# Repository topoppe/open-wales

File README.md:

# open-wales
Open-WaLeS: Ein Open-Source-IoT-System zur kurz- und langfristigen Überwachung von Binnenpegeln

Welcome to the official Github-Repo of the Open-WaLeS-System

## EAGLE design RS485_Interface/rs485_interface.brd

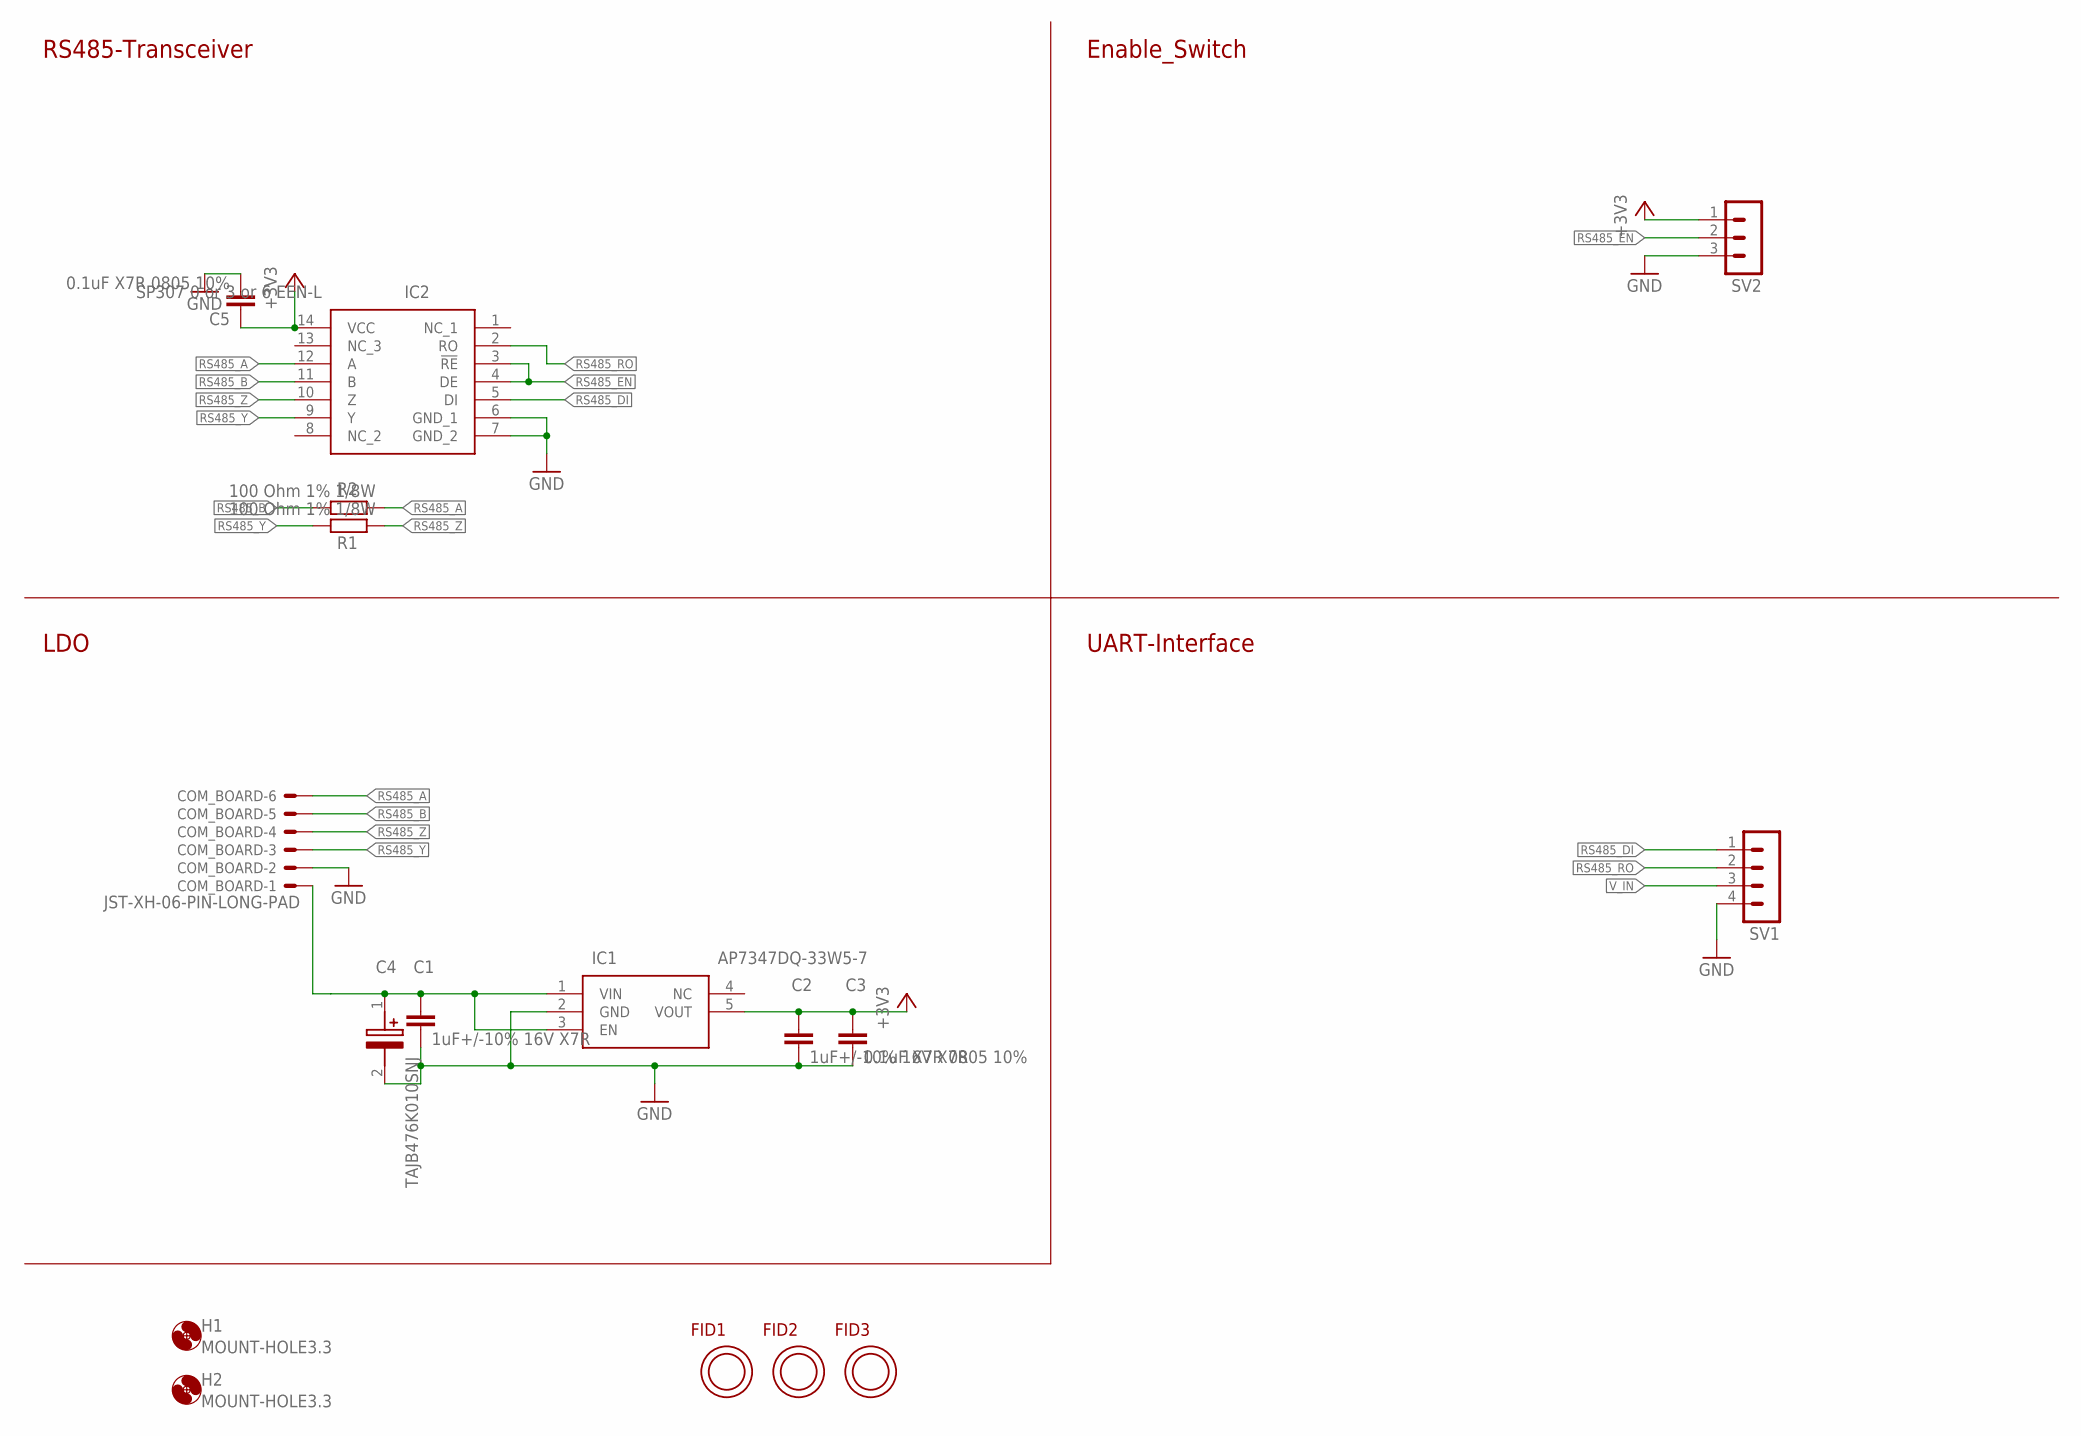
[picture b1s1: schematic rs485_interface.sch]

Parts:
C1, C2: 1uF+/-10% 16V X7R; C0805
C3, C5: 0.1uF X7R 0805 10%; C0805
C4: TAJB476K010SNJ; CAPPM3528X210N
COM_BOARD: JST-XH-06-PIN-LONG-PAD; JST-XH-06-PACKAGE-LONG-PAD
FID1, FID2, FID3: OPEN-PNP-FIDUCIAL
H1, H2: MOUNT-HOLE3.3; 3,3
IC1: AP7347DQ-33W5-7; SOT95P280X145-5N
IC2: SP307 0 or 3 or 6 EEN-L; SOIC127P600X175-14N
R1, R2: 100 Ohm 1% 1/8W; R0805
SV1: MA04-1
SV2: MA03-1

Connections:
+3V3: C2.1, C3.1, C5.1, IC1.5 (VOUT), IC2.14 (VCC), SV2.1
GND: C1.2, C2.2, C3.2, C4.2 (-), C5.2, COM_BOARD.2, IC1.2 (GND), IC2.6 (GND_1), IC2.7 (GND_2), SV1.4, SV2.3
RS485_A: COM_BOARD.6, IC2.12 (A), R2.1
RS485_B: COM_BOARD.5, IC2.11 (B), R2.2
RS485_DI: IC2.5 (DI), SV1.1
RS485_EN: IC2.3 (!RE), IC2.4 (DE), SV2.2
RS485_RO: IC2.2 (RO), SV1.2
RS485_Y: COM_BOARD.3, IC2.9 (Y), R1.2
RS485_Z: COM_BOARD.4, IC2.10 (Z), R1.1
V_IN: C1.1, C4.1 (+), COM_BOARD.1, IC1.1 (VIN), IC1.3 (EN), SV1.3

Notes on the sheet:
RS485-Transceiver
LDO
Enable_Switch
UART-Interface

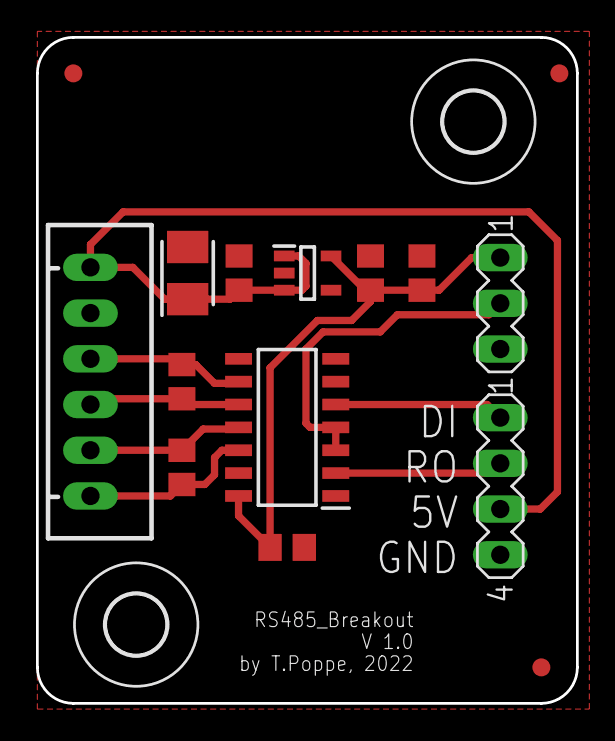
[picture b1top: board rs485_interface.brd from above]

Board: 2 copper layers, 30.0 x 37.0 mm, 17 parts (0 on the bottom side), 10 nets.

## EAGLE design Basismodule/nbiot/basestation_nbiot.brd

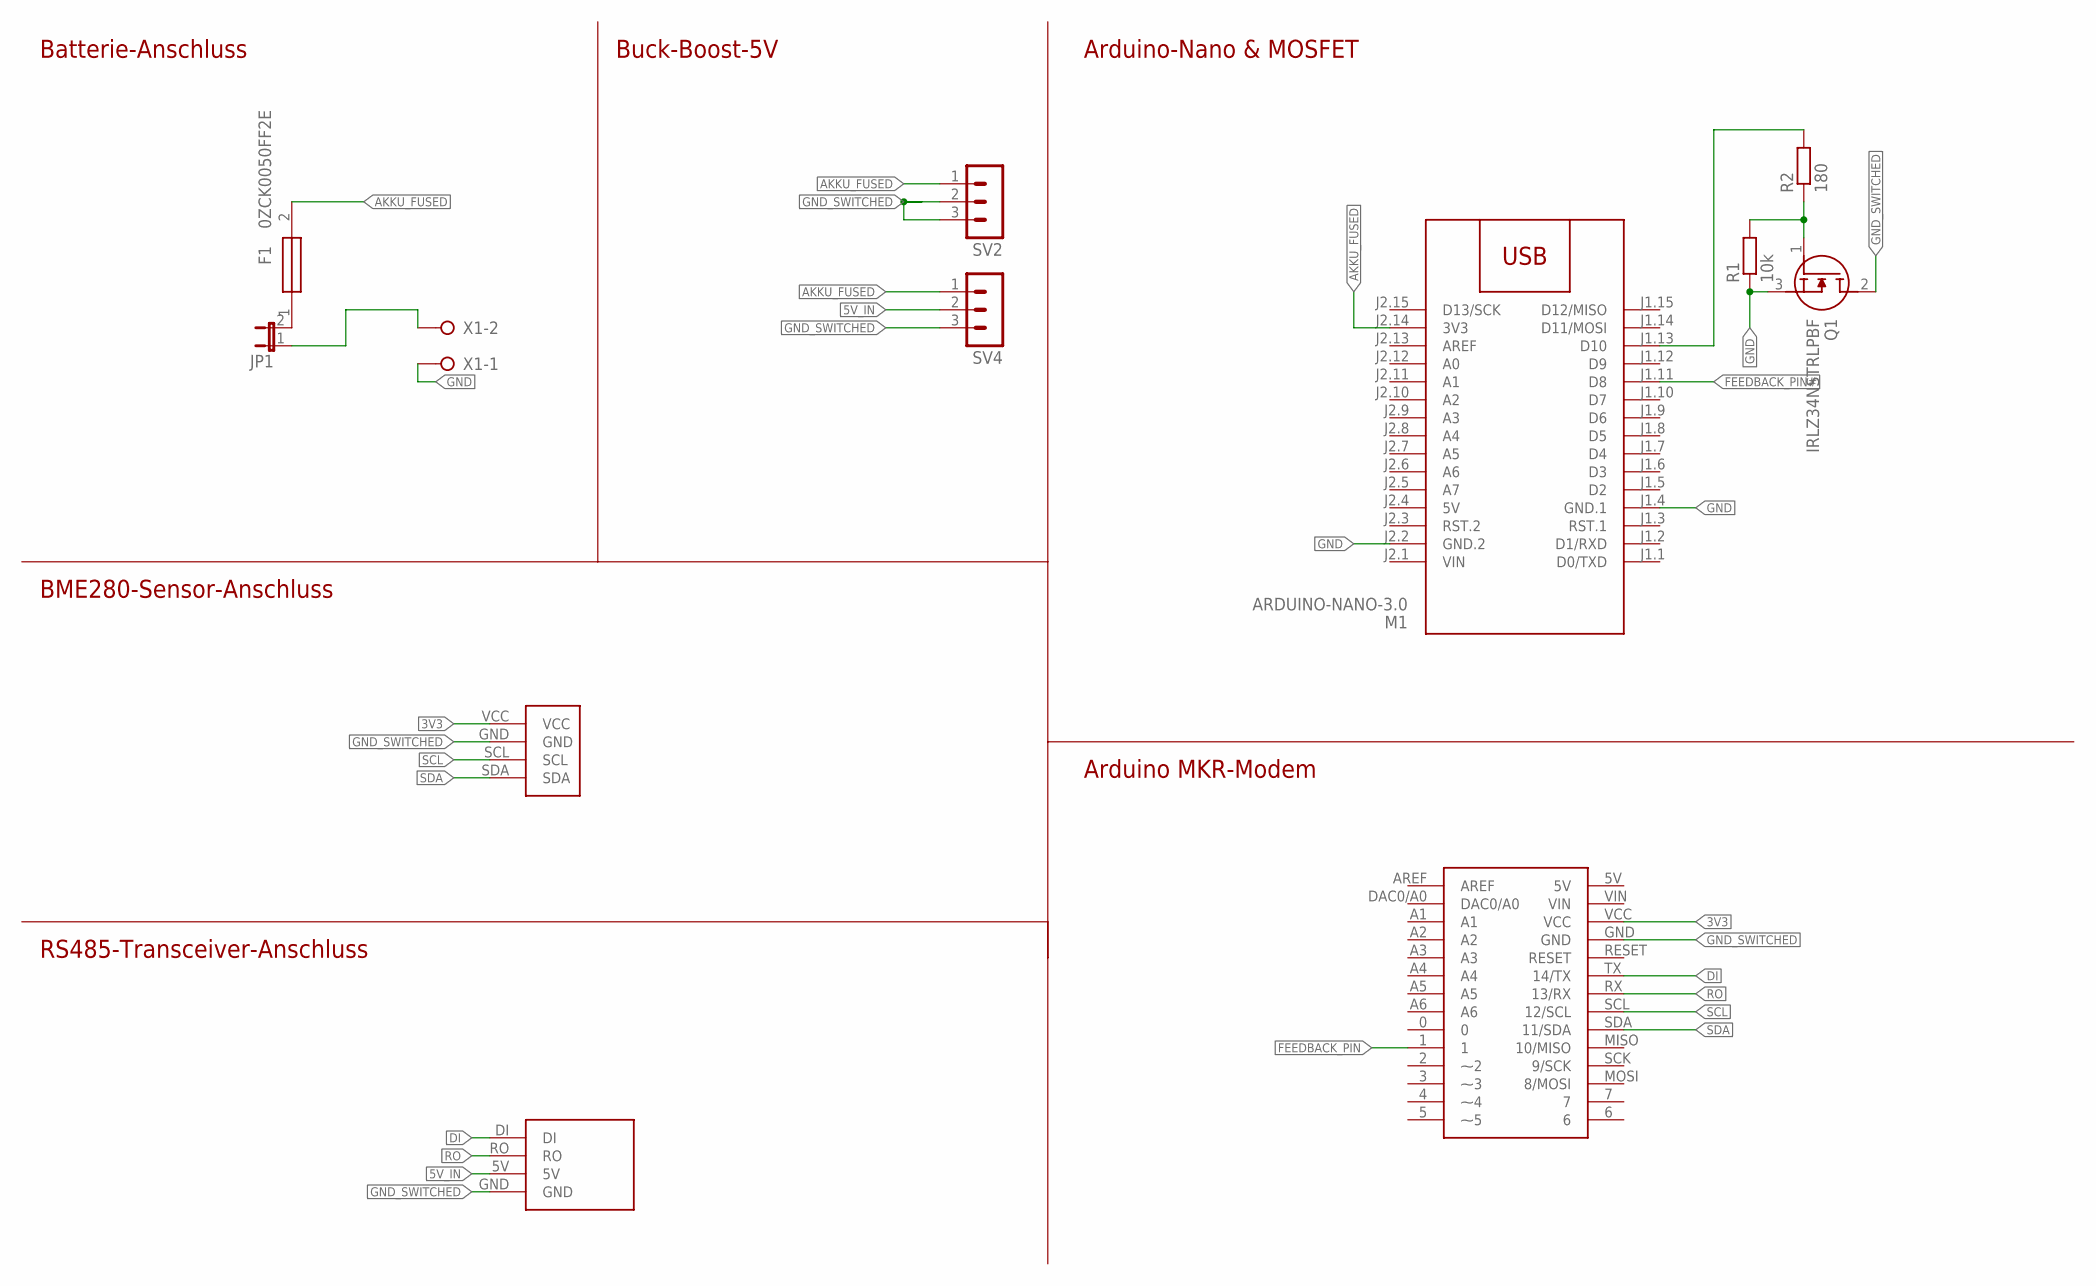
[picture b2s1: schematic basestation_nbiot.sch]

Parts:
F1: 0ZCK0050FF2E; FUSC2214X125N
JP1: JP1E; JP1
M1: ARDUINO-NANO-3.0
Q1: IRLZ34NSTRLPBF; D2PAK
R1: 10k; R1206
R2: 180; R1206
SV2, SV4: MA03-1
U$1: ARDUINO_GSM_MKR_1400; ARDUINO_GSM_MKR1400
U$2: BME280-BREAKOUT
U$3: RS485_PEGEL_BREAKOUT
X1: W237-02P; W237-132

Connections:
3V3: U$1.VCC, U$2.VCC
5V: M1.J2.4 (5V)
5V_IN: SV4.2, U$3.5V
AKKU_FUSED: F1.2, M1.J2.14 (3V3), SV2.1, SV4.1
AKKU_UNFUSED: JP1.1, X1.2
DI: U$1.TX (14/TX), U$3.DI
FEEDBACK_PIN: U$1.1
FEEDBACK_PIN#: M1.J1.11 (D8)
GND: M1.J1.4 (GND.1), M1.J2.2 (GND.2), Q1.3 (S), R1.1, X1.1
GND_SWITCHED: Q1.2 (D), SV2.2, SV2.3, SV4.3, U$1.GND, U$2.GND, U$3.GND
unnamed: M1.J1.13 (D10), R2.2
unnamed: Q1.1 (G), R1.2, R2.1
unnamed: F1.1, JP1.2
RO: U$1.RX (13/RX), U$3.RO
SCL: U$1.SCL (12/SCL), U$2.SCL
SDA: U$1.SDA (11/SDA), U$2.SDA
VIN: M1.J2.1 (VIN)

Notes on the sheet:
Batterie-Anschluss
Buck-Boost-5V
BME280-Sensor-Anschluss
RS485-Transceiver-Anschluss
Arduino-Nano & MOSFET
Arduino MKR-Modem

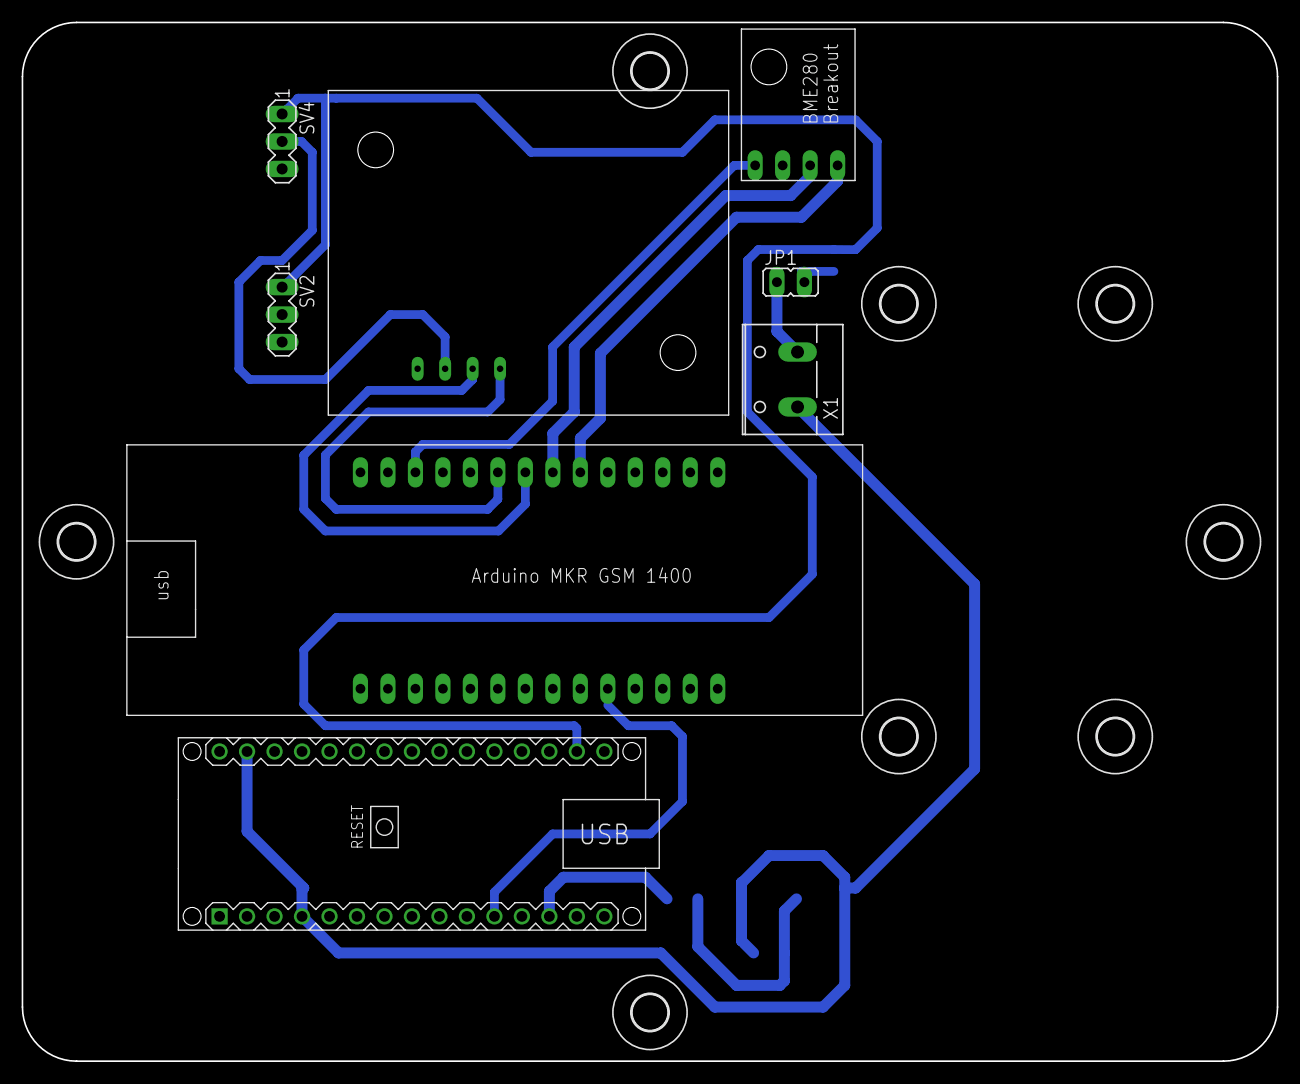
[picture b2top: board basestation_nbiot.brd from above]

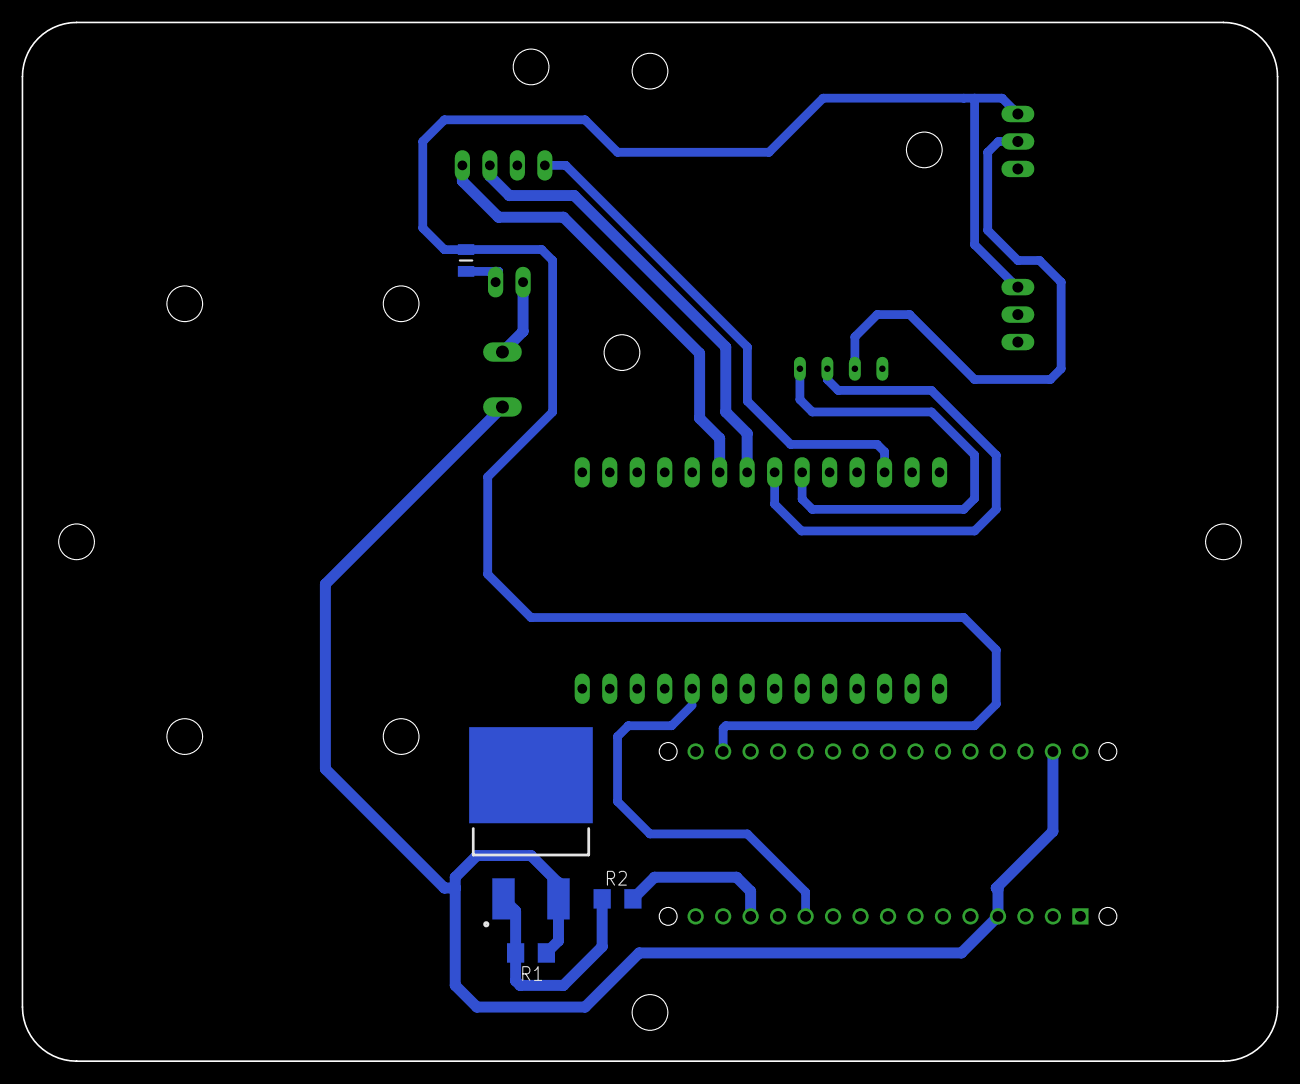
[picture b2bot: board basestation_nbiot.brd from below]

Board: 2 copper layers, 116.0 x 96.0 mm, 20 parts (4 on the bottom side), 13 nets.

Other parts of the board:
U$4, U$5, U$6, U$7, U$8, U$9, U$12, U$13: 3,3

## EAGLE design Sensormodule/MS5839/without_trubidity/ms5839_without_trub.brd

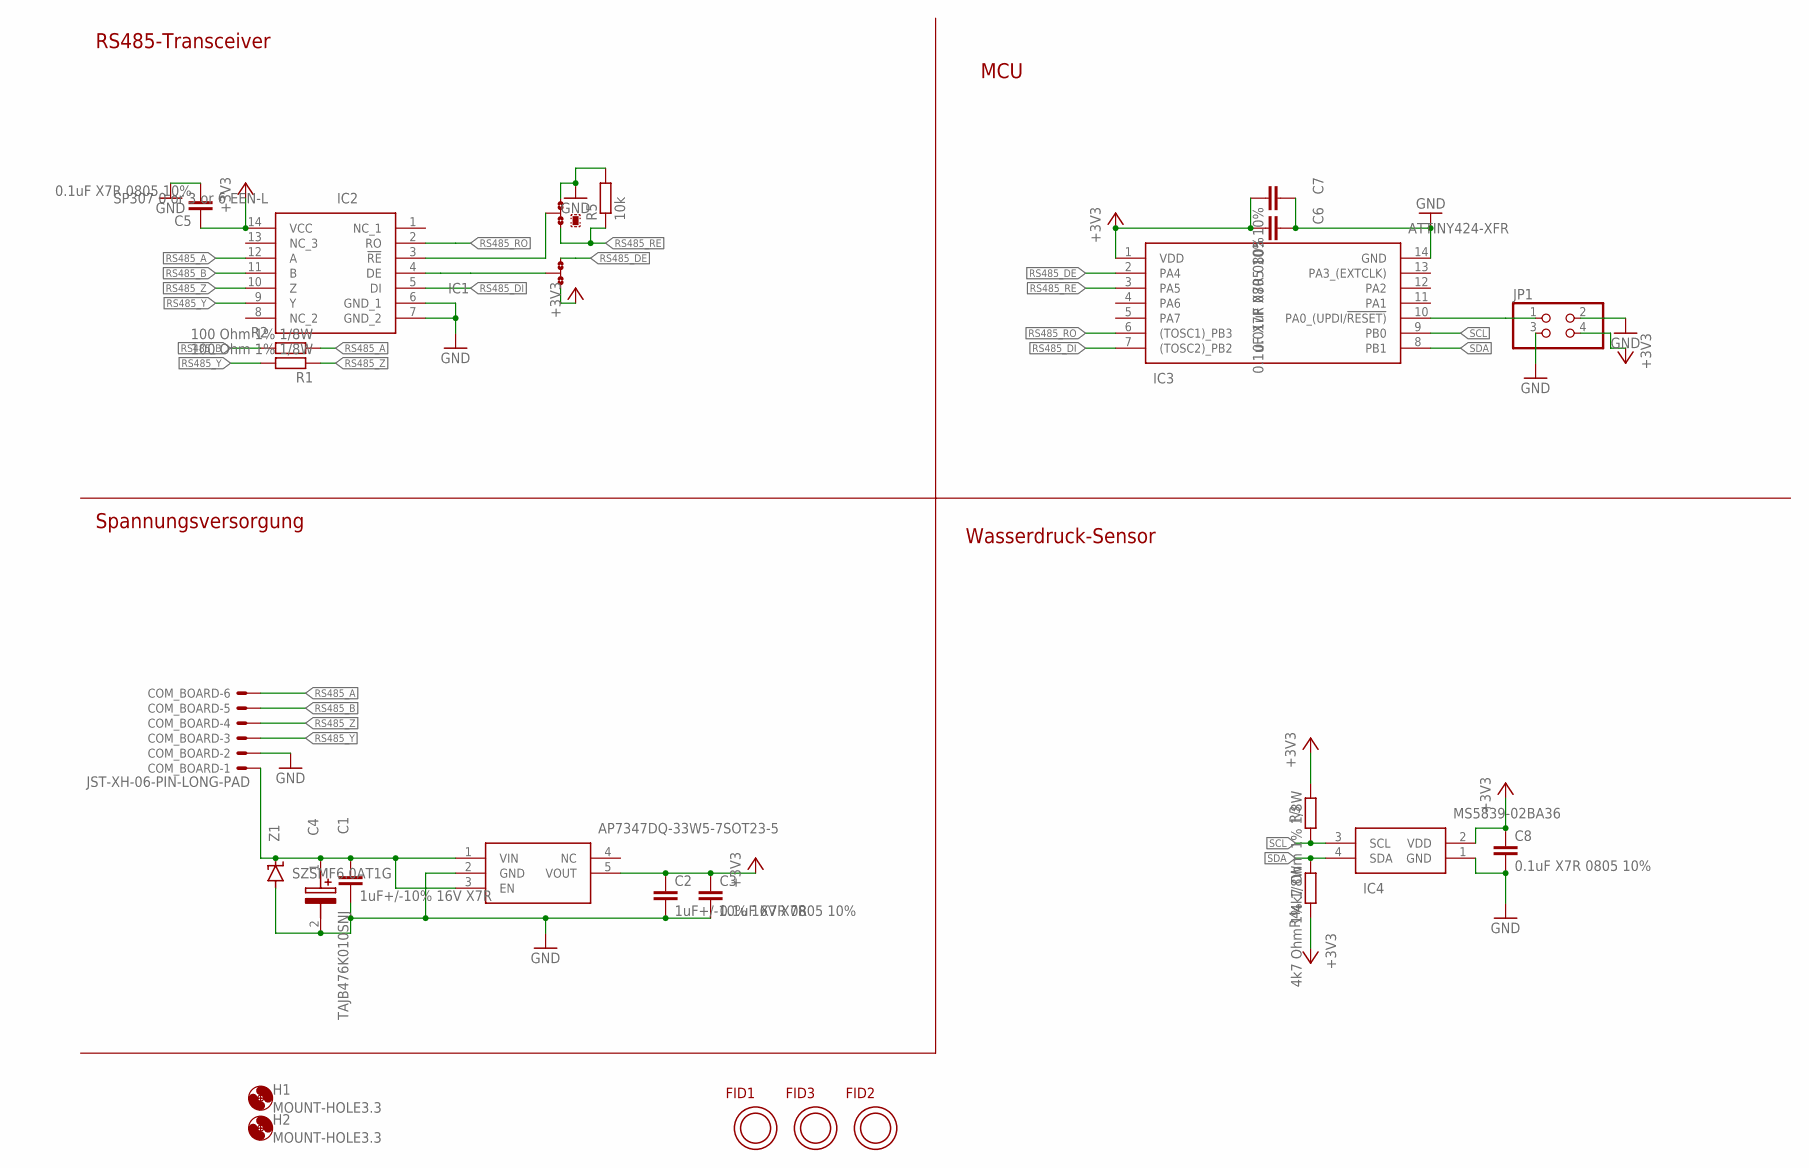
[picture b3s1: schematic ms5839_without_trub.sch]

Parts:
C1, C2: 1uF+/-10% 16V X7R; C0805
C3, C5, C6, C8: 0.1uF X7R 0805 10%; C0805
C4: TAJB476K010SNJ; CAPPM3528X210N
C7: 0.01uF X7R 0805 10%; C0805
COM_BOARD: JST-XH-06-PIN-LONG-PAD; JST-XH-06-PACKAGE-LONG-PAD
FID1, FID2, FID3: OPEN-PNP-FIDUCIAL
H1, H2: MOUNT-HOLE3.3; 3,3
IC1: AP7347DQ-33W5-7SOT23-5; SOT95P240X110-5N
IC2: SP307 0 or 3 or 6 EEN-L; SOIC127P600X175-14N
IC3: ATTINY424-XFR; SOP65P640X120-14N
IC4: MS5839-02BA36; MS583902BA36
JMP1, JMP2: 0R-JUMPA; A0R-JMP
JP1: PINHD-2X2; 2X02
R1, R2: 100 Ohm 1% 1/8W; R0805
R3, R4: 4k7 Ohm 1% 1/8W; R0805
R5: 10k; M0805
Z1: SZSMF6.0AT1G; SOD123

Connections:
!RE: IC2.3 (!RE), JMP2.2
+3V3: C2.1, C3.1, C5.1, C6.2, C7.2, C8.1, IC1.5 (VOUT), IC2.14 (VCC), IC3.1 (VDD), IC4.2 (VDD), JMP1.1, JP1.4, R3.1, R4.2
DE: IC2.4 (DE), JMP1.2
GND: C1.2, C2.2, C3.2, C4.2 (-), C5.2, C6.1, C7.1, C8.2, COM_BOARD.2, IC1.2 (GND), IC2.6 (GND_1), IC2.7 (GND_2), IC3.14 (GND), IC4.1 (GND), JMP2.3, JP1.2, JP1.3, R5.2, Z1.A
unnamed: C1.1, C4.1 (+), COM_BOARD.1, IC1.1 (VIN), IC1.3 (EN), Z1.C
unnamed: IC3.10 (PA0_(UPDI/!RESET)), JP1.1
RS485_A: COM_BOARD.6, IC2.12 (A), R2.1
RS485_B: COM_BOARD.5, IC2.11 (B), R2.2
RS485_DE: IC3.2 (PA4), JMP1.3
RS485_DI: IC2.5 (DI), IC3.7 ((TOSC2)_PB2)
RS485_RE: IC3.3 (PA5), JMP2.1, R5.1
RS485_RO: IC2.2 (RO), IC3.6 ((TOSC1)_PB3)
RS485_Y: COM_BOARD.3, IC2.9 (Y), R1.2
RS485_Z: COM_BOARD.4, IC2.10 (Z), R1.1
SCL: IC3.9 (PB0), IC4.3 (SCL), R3.2
SDA: IC3.8 (PB1), IC4.4 (SDA), R4.1

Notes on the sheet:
RS485-Transceiver
Spannungsversorgung
MCU
Wasserdruck-Sensor

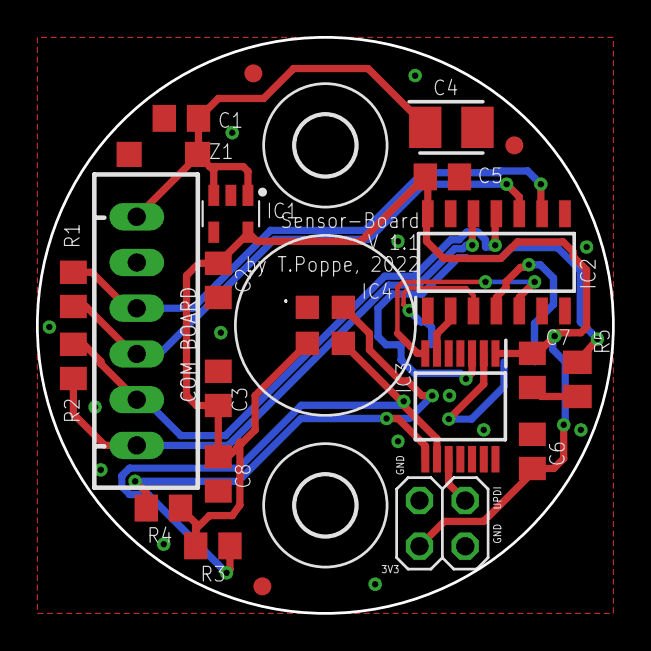
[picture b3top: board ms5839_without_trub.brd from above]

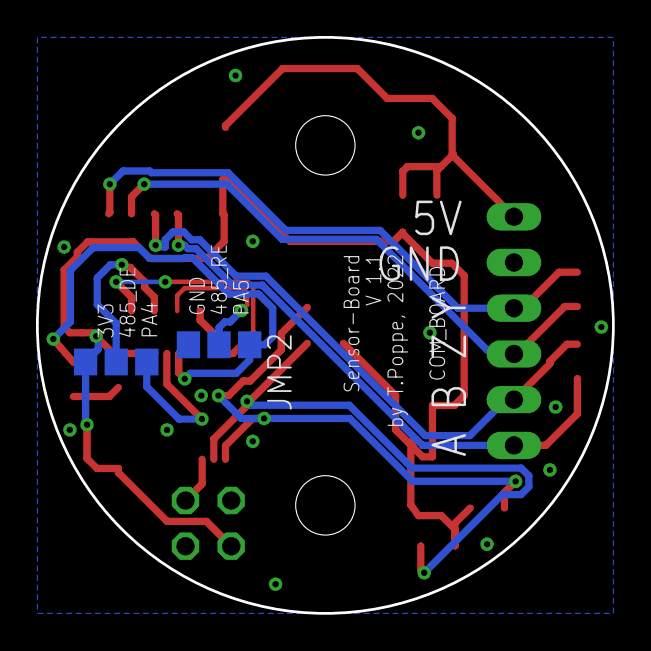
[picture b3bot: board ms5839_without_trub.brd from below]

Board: 2 copper layers, 32.0 x 32.0 mm, 27 parts (2 on the bottom side), 16 nets.

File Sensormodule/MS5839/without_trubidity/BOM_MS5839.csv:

Qty;Value;Parts;MOUSER_PART_NUMBER
2;1uF+/-10% 16V X7R;C1, C2;710-885012207078 
4;0.1uF X7R 0805 10%;C3, C5, C6, C8; 80-C0805C104K5RACLR
1;TAJB476K010SNJ;C4;581-TAJB476K010SNJ
1;0.01uF X7R 0805 10%;C7;710-885382207009
1;AP7347DQ-33W5-7SOT23-5;IC1;621-AP7347DQ-33W5-7
1;SP307 0 or 3 or 6  EEN-L;IC2;701-SP3076EEN-L
1;ATTINY424-XFR;IC3;579-ATTINY824-XFR
1;MS5839-02BA36;IC4;824-MS5839-02BA36
2;100 Ohm 1% 1/8W;R1, R2;603-RC0805FR-13100RL
2;4k7 Ohm 1% 1/8W;R3, R4;71-CRCW08054K70FKEAC
1;10k;R5;71-CRCW080510K0FKEAC
1;SZSMF6.0AT1G;Z1;863-SZSMF6.0AT1G

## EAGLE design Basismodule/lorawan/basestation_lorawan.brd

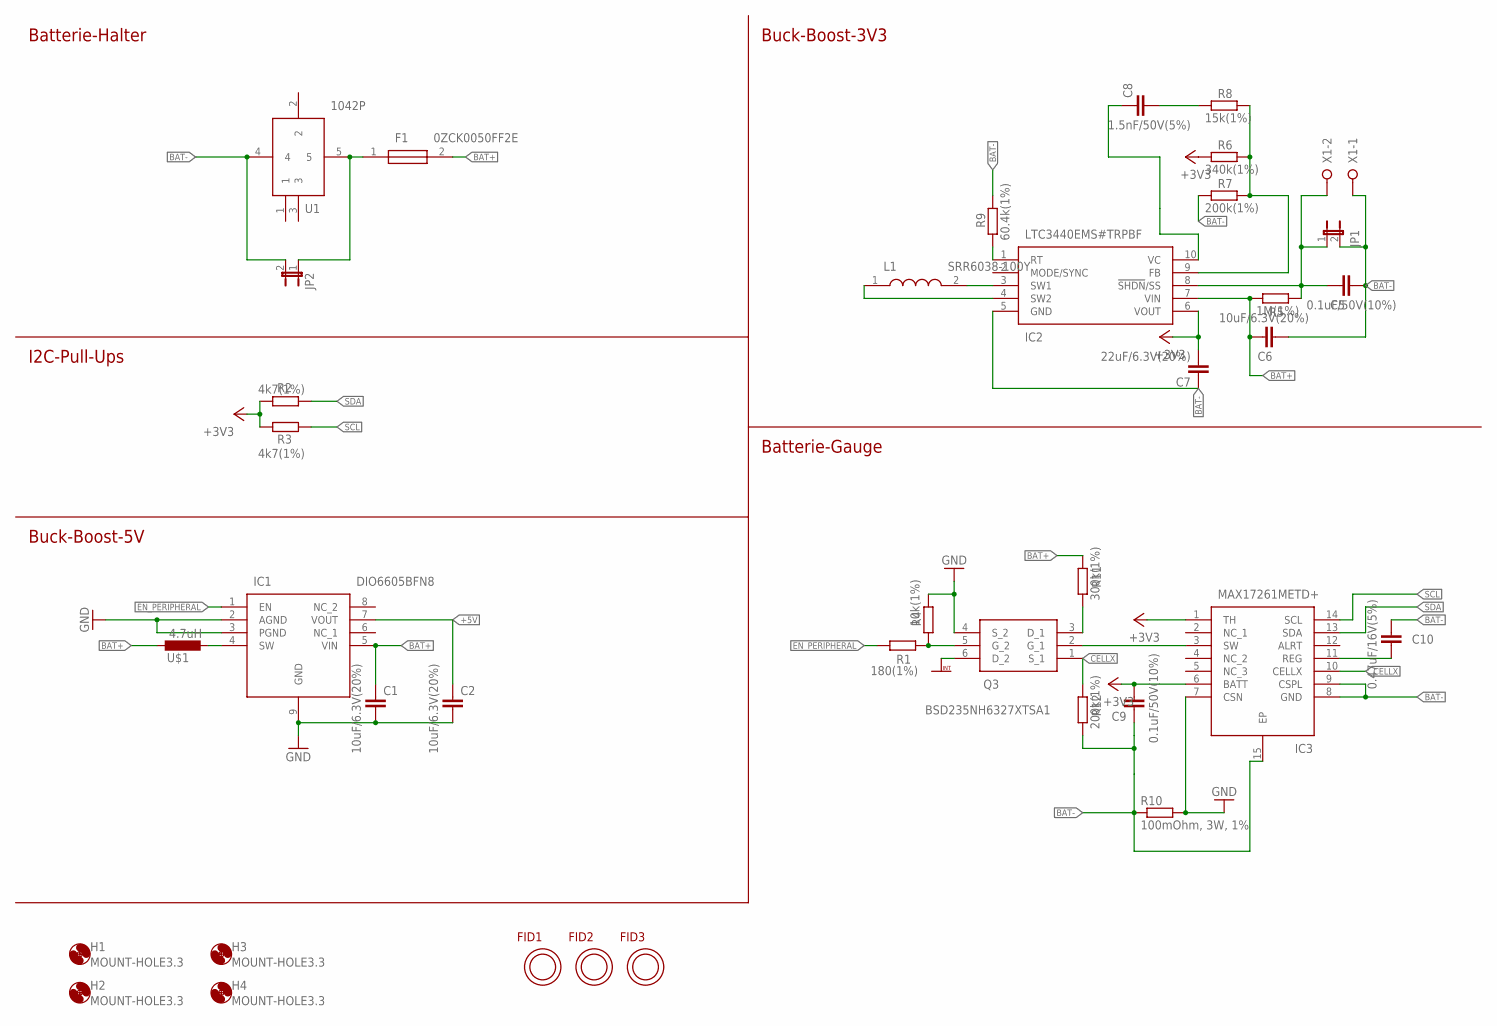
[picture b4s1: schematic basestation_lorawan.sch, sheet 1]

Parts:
C1, C2, C6: 10uF/6.3V(20%); C0805; MOUSER 963-JMK212BJ106MG-T
C5, C9: 0.1uF/50V(10%); C0805; MOUSER 80-C0805C104K5RACLR
C7: 22uF/6.3V(20%); C0805K; MOUSER 710-885012107005
C8: 1.5nF/50V(5%); C0805; MOUSER 80-C0805C152J5GAC
C10: 0.47uF/16V(5%); C0805; MOUSER 77-VJ0805Y474JXJTBC
F1: 0ZCK0050FF2E; FUSC2214X125N; MOUSER 530-0ZCK0050FF2E
FID1, FID2, FID3: OPEN-PNP-FIDUCIAL
H1, H2, H3, H4: MOUNT-HOLE3.3; 3,3
IC1: DIO6605BFN8; SON50P300X200X80-9N
IC2: LTC3440EMS#TRPBF; SOP50P490X110-10N
IC3: MAX17261METD+; SON40P300X300X80-15N
JP1, JP2: JP1E; JP1
L1: SRR6038-100Y; SRR6038330Y; MOUSER_PART_NUMBER 652-SRR6038-100Y
Q3: BSD235NH6327XTSA1; SOT65P210X100-6N
R1: 180(1%); M0805
R2, R3: 4k7(1%); M0805
R4: 10k(1%); M0805
R5: 1M(1%); M0805
R6: 340k(1%); M0805
R7, R12: 200k(1%); M0805
R8: 15k(1%); M0805
R9: 60.4k(1%); M0805
R10: 100mOhm, 3W, 1%; R2512; MOUSER 652-CRA2512FZR100ELF
R11: 300k(1%); M0805
U1: 1042P
U$1: 4.7uH; R0805; MOUSER 963-MBMK2520T4R7M
X1: W237-02P; W237-132

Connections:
+3V3: C7.2, C9.2, IC2.6 (VOUT), IC3.1 (TH), IC3.6 (BATT), R2.2, R3.2, R6.1; also elsewhere on the board
+5V: C2.1, IC1.7 (VOUT); also elsewhere on the board
BAT+: C1.1, C6.2, F1.2, IC1.5 (VIN), IC2.7 (VIN), R5.1, R11.2, U$1.1
BAT+_UNFUSED: F1.1, JP2.1, U1.5
BAT-: C5.2, C6.1, C7.1, C9.1, C10.1, IC2.5 (GND), IC3.8 (GND), IC3.9 (CSPL), IC3.15 (EP), JP1.2, JP2.2, R7.1, R9.2, R10.1, R12.1, U1.4, X1.1
CELLX: IC3.10 (CELLX), Q3.1 (S_1), R12.2
EN_PERIPHERAL: IC1.1 (EN), R1.2; also elsewhere on the board
GND: C1.2, C2.2, IC1.2 (AGND), IC1.3 (PGND), IC1.9 (GND), IC3.7 (CSN), Q3.4 (S_2), R4.2, R10.2; also elsewhere on the board
GNDINT: Q3.6 (D_2); also elsewhere on the board
unnamed: IC1.4 (SW), U$1.2
unnamed: Q3.5 (G_2), R1.1, R4.1
unnamed: IC2.3 (SW1), L1.2
unnamed: IC2.4 (SW2), L1.1
unnamed: IC2.9 (FB), R6.2, R7.2, R8.2
unnamed: C5.1, IC2.8 (!SHDN!/SS), JP1.1, R5.2, X1.2
unnamed: C8.2, R8.1
unnamed: C8.1, IC2.10 (VC)
unnamed: Q3.3 (D_1), R11.1
REG: C10.2, IC3.11 (REG)
RT: IC2.1 (RT), R9.1
SCL: IC3.14 (SCL), R3.1; also elsewhere on the board
SDA: IC3.13 (SDA), R2.1; also elsewhere on the board
SW: IC3.3 (SW), Q3.2 (G_1)

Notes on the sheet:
Batterie-Halter
I2C-Pull-Ups
Buck-Boost-5V
Buck-Boost-3V3
Batterie-Gauge

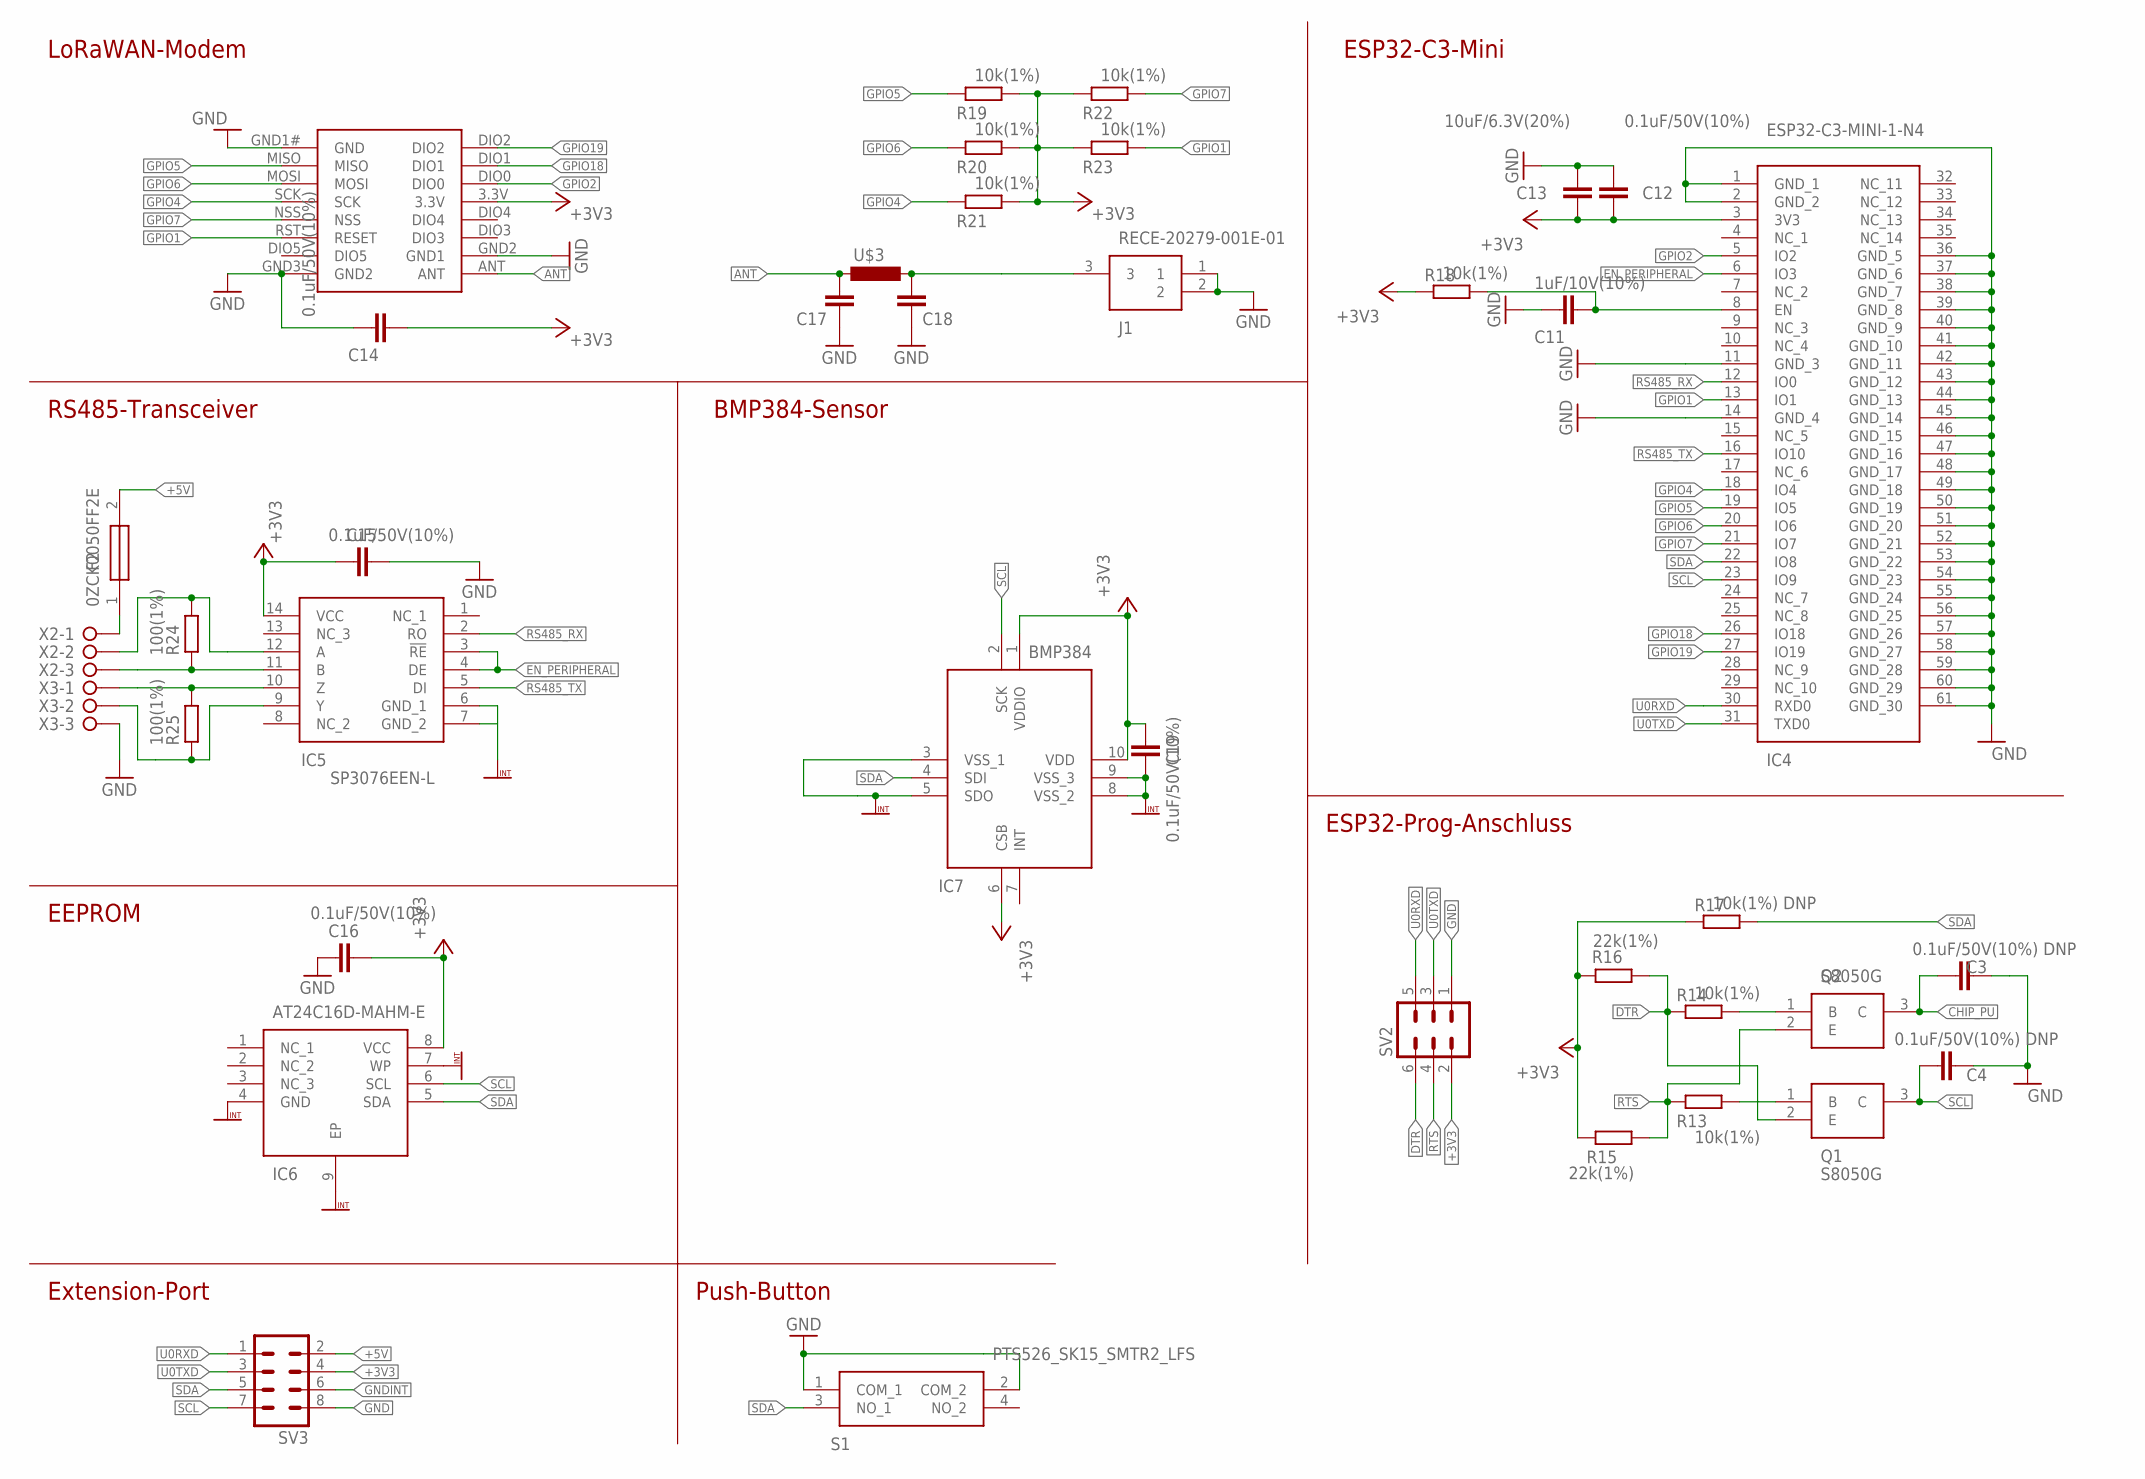
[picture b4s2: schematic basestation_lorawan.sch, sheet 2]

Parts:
C3, C4: 0.1uF/50V(10%) DNP; C0805; MOUSER 80-C0805C104K5RACLR
C11: 1uF/10V(10%); C0805; MOUSER 710-885012207078
C12, C14, C15, C16, C19: 0.1uF/50V(10%); C0805; MOUSER 80-C0805C104K5RACLR
C13: 10uF/6.3V(20%); C0805; MOUSER 963-JMK212BJ106MG-T
C17, C18: C-EUC0805K; C0805K
F2: 0ZCK0050FF2E; FUSC2214X125N; MOUSER 530-0ZCK0050FF2E
IC4: ESP32-C3-MINI-1-N4; ESP32C3MINI1N4; MOUSER 356-ESP32-C3-MINI1N4
IC5: SP3076EEN-L; SOIC127P600X175-14N
IC6: AT24C16D-MAHM-E; SON50P300X200X60-9N; MOUSER 579-AT24C16D-MAHM-E
IC7: BMP384
J1: RECE-20279-001E-01; RECE.20279.001E.01; MOUSER 960-RECE20279001E01
Q1, Q2: S8050G; SOT95P240X110-3N; MOUSER 750-SS8050-G
R13, R14, R18, R19, R20, R21, R22, R23: 10k(1%); M0805
R15, R16: 22k(1%); M0805
R17: 10k(1%) DNP; M0805
R24, R25: 100(1%); M0805
S1: PTS526_SK15_SMTR2_LFS; PTS526SK15SMTR2LFS; MOUSER 611-PTS526SK15SMR2L
SV2: MA03-2
SV3: MA04-2
U$2: RFM95W
U$3: L-0805; R0805
X2, X3: W237-3E

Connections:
+3V3: C12.1, C13.2, C14.1, C15.1, C16.2, C19.1, IC4.3 (3V3), IC5.14 (VCC), IC6.8 (VCC), IC7.1 (VDDIO), IC7.6 (CSB), IC7.10 (VDD), R15.2, R16.1, R17.2, R18.2, R19.1, R20.1, R21.1, R22.2, R23.2, SV2.2, SV3.4, U$2.3.3V; also elsewhere on the board
+5V: F2.2, SV3.2; also elsewhere on the board
A: IC5.12 (A), R24.2, X2.2
ANT: C17.1, U$2.ANT, U$3.1
B: IC5.11 (B), R24.1, X2.3
CHIP_PU: C3.2, C11.1, IC4.8 (EN), Q2.3 (C), R18.1
DTR: Q1.2 (E), R14.2, R16.2, SV2.6
EN_PERIPHERAL: IC4.6 (IO3), IC5.3 (!RE), IC5.4 (DE); also elsewhere on the board
GND: C3.1, C4.1, C11.2, C12.2, C13.1, C14.2, C15.2, C16.1, C17.2, C18.2, IC4.1 (GND_1), IC4.2 (GND_2), IC4.11 (GND_3), IC4.14 (GND_4), IC4.36 (GND_5), IC4.37 (GND_6), IC4.38 (GND_7), IC4.39 (GND_8), IC4.40 (GND_9), IC4.41 (GND_10), IC4.42 (GND_11), IC4.43 (GND_12), IC4.44 (GND_13), IC4.45 (GND_14), IC4.46 (GND_15), IC4.47 (GND_16), IC4.48 (GND_17), IC4.49 (GND_18), IC4.50 (GND_19), IC4.51 (GND_20), IC4.52 (GND_21), IC4.53 (GND_22), IC4.54 (GND_23), IC4.55 (GND_24), IC4.56 (GND_25), IC4.57 (GND_26), IC4.58 (GND_27), IC4.59 (GND_28), IC4.60 (GND_29), IC4.61 (GND_30), J1.1, J1.2, S1.1 (COM_1), S1.2 (COM_2), SV2.1, SV3.8, U$2.GND1# (GND), U$2.GND2 (GND1), U$2.GND3 (GND2), X3.3; also elsewhere on the board
GNDINT: C19.2, IC5.6 (GND_1), IC5.7 (GND_2), IC6.4 (GND), IC6.7 (WP), IC6.9 (EP), IC7.3 (VSS_1), IC7.5 (SDO), IC7.8 (VSS_2), IC7.9 (VSS_3), SV3.6; also elsewhere on the board
GPIO1: IC4.13 (IO1), R23.1, U$2.RST (RESET)
GPIO2: IC4.5 (IO2), U$2.DIO0
GPIO4: IC4.18 (IO4), R21.2, U$2.SCK
GPIO5: IC4.19 (IO5), R19.2, U$2.MISO
GPIO6: IC4.20 (IO6), R20.2, U$2.MOSI
GPIO7: IC4.21 (IO7), R22.1, U$2.NSS
GPIO18: IC4.26 (IO18), U$2.DIO1
GPIO19: IC4.27 (IO19), U$2.DIO2
unnamed: Q2.1 (B), R14.1
unnamed: Q1.1 (B), R13.1
unnamed: F2.1, X2.1
unnamed: C18.1, J1.3, U$3.2
RS485_RX: IC4.12 (IO0), IC5.2 (RO)
RS485_TX: IC4.16 (IO10), IC5.5 (DI)
RTS: Q2.2 (E), R13.2, R15.1, SV2.4
SCL: C4.2, IC4.23 (IO9), IC6.6 (SCL), IC7.2 (SCK), Q1.3 (C), SV3.7; also elsewhere on the board
SDA: IC4.22 (IO8), IC6.5 (SDA), IC7.4 (SDI), R17.1, S1.3 (NO_1), SV3.5; also elsewhere on the board
U0RXD: IC4.30 (RXD0), SV2.5, SV3.1
U0TXD: IC4.31 (TXD0), SV2.3, SV3.3
Y: IC5.9 (Y), R25.1, X3.2
Z: IC5.10 (Z), R25.2, X3.1

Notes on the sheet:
ESP32-C3-Mini
ESP32-Prog-Anschluss
LoRaWAN-Modem
RS485-Transceiver
EEPROM
Extension-Port
Push-Button
BMP384-Sensor

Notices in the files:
parts and their libraries:
diy-modules: Released under the Creative Commons Attribution 4.0 International License: http://creativecommons.org/licenses/by/4.0
